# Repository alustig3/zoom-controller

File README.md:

# Table of Contents

- [What is this?](#what-is-this)
  - [Demo Video](#demo-video)
- [How do I use it?](#how-do-i-use-it)
  - [Turning on](#turning-on)
  - [Connecting to Bluetooth](#connecting-to-bluetooth)
  - [Turning off](#turning-off)
  - [Disconnecting Bluetooth](#disconnecting-bluetooth)
  - [Adjust volume](#adjust-volume)
  - [Controlling Zoom!](#controlling-zoom)
  - [Switching modes](#switching-modes)
- [Getting fancy](#getting-fancy)
  - [Desktop notifications](#desktop-notifications)
  - [YouTube controller](#youtube-controller)
- [How do I make one?](#how-do-i-make-one)
  - [Stand](#stand)
  - [Electronics](#electronics)
  - [Additional hardware](#additional-hardware)
  - [Software](#software)
- [Feedback](#feedback)
# What is this?
I, like many others, found myself using Zoom video conference software a lot this past year. 
I created this device to make interacting with Zoom faster and more pleasant. 

- The Zoom Controller connects with your computer over Bluetooth and emulates keyboard key presses
- Works with Mac and Windows
- Five buttons are setup to emulate the default keyboard shortcuts in Zoom
- A knob controls the computer's media volume
- Powered by two AA batteries
- The circuit board mounts to a bent piece of 12 Gauge steel
- Bonus features include desktop notifications and YouTube Mode (see [getting fancy](#getting-fancy))

## Demo video
<div style="">
  
</div>

# How do I use it? 
- [Turning on](#turning-on)
- [Connecting to Bluetooth](#connecting-to-bluetooth)
- [Turning off](#turning-off)
- [Disconnecting Bluetooth](#disconnecting-bluetooth)
- [Controlling Zoom!](#controlling-zoom)
- [Switching modes](#switching-modes)

## Turning on
Press and hold the **VOLUME** knob to turn on. 
You can let go of the knob as soon as you see it light up red. 
The knob will "breathe" red light while it is trying to connect to Bluetooth. Once connected, the knob will turn green. 

The controller will automatically turn off after 20 seconds attempting and failing to connect.

## Connecting to Bluetooth
If it is the first time using Zoom Controller, you will need to add it your computer's list of Bluetooth devices. Once added, the Zoom Controller will automatically connect when turned on and within range of your computer.
### Mac
- Open System Preferences -> Bluetooth
- [Turn on](#turning-on) Zoom Controller
- When it appears in your list of Bluetooth devices, click connect. Once connected, the light will turn green, and you're good to go!
- There may be a "Keyboard Setup Assistant" window that pops up asking you to press a key to identify your keyboard. You can ignore this and just close the window.

### Windows
- Search for "bluetooth" in the search bar and select "Bluetooth and other devices settings"
- At the top, click "Add Bluetooth or other device"
- Click "Bluetooth - Mice, keyboards, pens or other kinds of Bluetooth devices"
- Turn on the Zoom Controller by pressing the **VOLUME** knob until a red light appears
- Zoom controller should appear in the "Add a device" list

## Turning off
Press and hold the **LEAVE** button. The volume knob's light will turn off when the controller is powered off.

There is an idle clock always counting. 
Every time you press a button or rotate the knob, the idle clock is reset to 0. 
If the idle clock reaches 60 minutes, the controller will automatically turn itself off to save battery.

## Disconnecting Bluetooth
The Zoom Controller can only be connected to one device at a time. If you want to use it with a different computer it is important that you first remove it from its current computer's Bluetooth device list.
### Mac
- Open to System Prefrences -> Bluetooth
- Right click on the Zoom Controller and select "Remove"
### Windows
- Search for "bluetooth" in the search bar and select "Bluetooth and other devices settings"
- Under the "Mouse, keyboard, & pen" click "Zoom Controller" and then click "Remove device"

## Controlling Zoom!

### Adjust volume
Rotate the **VOLUME** knob clockwise to increase volume, counterclockwise to decrease volume.

### Send Shortcuts on Mac
The five buttons are setup to execute the following Zoom functions by emulating their default keyboard shortcuts.

| Button | Zoom Function             | Emulated Mac Keypress                           |
|--------|---------------------------|-------------------------------------------------|
| Mic    | mute/unmute microphone    | shift + command + a                             |
| Camera | start/stop video          | shift + command + v                             |
| Share  | start/stop screen sharing | shift + command + s                             |
| View   | speaker/gallery view      | shift + command + w                             |
| Leave* | leave meeting             | command + w, followed by Return to confirm leave |

### Send Shortcuts on Windows

| Button              | Zoom Function             | Emulated Windows Keypress                  |
|---------------------|---------------------------|--------------------------------------------|
| Mic                 | mute/unmute microphone    | alt + a                                    |
| Camera              | start/stop video          | alt + v                                    |
| Share               | start/stop screen sharing | alt + s                                    |
| View (single press) | speaker view              | alt + F1                                   |
| View (double press) | gallery view              | alt + F2                                   |
| Leave*              | leave meeting             | alt + q, folowed by Enter to confirm leave |

**Zoom Controller will automatically turn off 8 seconds after pressing **LEAVE**, unless you keep it awake by pressing a button or rotating the knob within those 8 seconds. 
The knob will blink green indicating that the controller is about to turn itself off.*

## Switching modes
Keyboard shortcuts sent by Zoom Controller depend on which operating system and which application is being used. 
Because of this, there are 4 different modes that Zoom controller can be in. 
There are 2 operating system modes (Mac, Windows) and 2 application modes (Zoom, YouTube*).

**see [YouTube Controller](#youtube-controller)*

### Mac mode
- Press down the **VOLUME** button. 
- While holding the **VOLUME** button, press and hold the **MIC** button for 2 seconds
- The **VOLUME** button will blink **3** times indicating it is now in Mac mode. You can release both buttons.

### Windows mode
- Press down the **VOLUME** button. 
- While holding the **VOLUME** button, press and hold the **CAMERA** button for 2 seconds
- The **VOLUME** button will blink **7** times indicating it is now in Windows mode. You can release both buttons.

### Switch into Zoom mode
- Press and hold the VOLUME knob
- Press and release the MIC button

### Switch into YouTube mode
- Press and hold the VOLUME knob
- Press and release the CAMERA button

# Getting fancy
## Desktop notifications
You can enable Zoom Controller notifications show up on your desktop. The following notifications will appear when relevant:
- "Mac Mode"
- "Windows Mode"
- "Zoom Mode"
- "YouTube Mode"
- "Controller has been idle for awhile and will soon turn itself off. Press any button or rotate knob to keep awake"
### Mac notifications setup
- Download [Hammerspoon](https://www.hammerspoon.org/).
- Click the Hammerspooon menu bar icon and select "Open Config".
- Add the following to your `init.lua` file:
```lua
hs.hotkey.bind({"cmd", "alt", "ctrl"}, "F1", function()
  hs.alert.show("Mac Mode")
end)

hs.hotkey.bind({"cmd", "alt", "ctrl"}, "F2", function()
  hs.alert.show("Windows Mode")
end)

hs.hotkey.bind({"cmd","alt","ctrl"}, "F3", function()
  hs.notify.new({title="Zoom Controller Idle", informativeText="Controller will turn off soon\nPress any key to keep awake"}):send()
end))

hs.hotkey.bind({"cmd", "alt", "ctrl"}, "F4", function()
  hs.alert.show("Zoom Mode")
end)

hs.hotkey.bind({"cmd", "alt", "ctrl"}, "F5", function()
  hs.alert.show("YouTube Mode")
end)

```
- Save your changes to the `inti.lua` file then click the Hammerspoon menu bar icon and select "Reload Config" 
### Windows notifications setup
- Download [AutoHotkey](https://www.autohotkey.com/)
- Download this [zoom_controller_notifications.ahk](docs/zoom_controller_notifications.ahk) script file
- Once the script file is downloaded, double click it to begin running the script
- If you want the script to automatically run every time you turn on your computer, follow instructions [here](https://www.autohotkey.com/docs/FAQ.htm#Startup)

## YouTube controller
I've found this device to be super useful for watching online videos.

### Installation
- Add an extension called **Video Speed Controller** to your web browser
  - [Chrome extension](https://chrome.google.com/webstore/detail/video-speed-controller/nffaoalbilbmmfgbnbgppjihopabppdk)
  - [Firefrox extension](https://addons.mozilla.org/en-US/firefox/addon/videospeed/?utm_source=addons.mozilla.org&utm_medium=referral&utm_content=search)

### Controlling YouTube
#### Send Shortcuts
| Button | YouTube Function  | Emulated Keypress |
|--------|-------------------|-------------------|
| Mic    |                   |                   |
| Camera | rewind 10s        | z                 |
| Share  | fast forward 10s  | x                 |
| View   | toggle fullscreen | f                 |
| Leave  | play/pause        | spacebar          |

#### Adjust playback speed
- Increase/decrease the video playback speed by rotating the VOLUME knob clockwise/counterclockwise
- Toggle between 1X speed and your adjusted playback speed by clicking the VOLUME knob
#### Adjust Volume
- Increase/decrease the volume by pressing and holding down MIC then rotating the VOLUME knob clockwise/counterclockwise.

# How do I make one?
## Stand
- File for lasercutting: [stand.dxf](https://alustig3.github.io/zoom-controller/stand.dxf)
- 0.1" thick (12Ga) steel cut and bent at https://www.oshcut.com/

## Electronics
### Bill of Materials
| Qty | Reference          | Description       | Value/MPN                                                                                                    | 
|-----|--------------------|-------------------|--------------------------------------------------------------------------------------------------------------|
| 1   | BT1                | Battery Holder    | [2462](https://www.digikey.com/product-detail/en/keystone-electronics/2466/36-2466-ND/303815)                | 
| 1   | C1                 | 0805 Capacitor    | 10nF                                                                                                         | 
| 1   | D1                 | Schottky Diode    | [BAT54C](http://www.diodes.com/_files/datasheets/ds11005.pdf)                                                | 
| 2   | H3, H4             | Threaded Standoff | [4207](https://www.adafruit.com/product/4207)                                                                | 
| 1   | Q1                 | P-Channel MOSFET  | [FDN340P](https://www.digikey.com/products/en?keywords=FDN340PCT-ND)                                         | 
| 1   | Q2                 | N-Channel MOSFET  | [BSS123](https://www.digikey.com/products/en?keywords=BSS123LT1GOSCT-ND)                                     | 
| 1   | R1                 | 0805 Resistor     | 100KΩ                                                                                                        | 
| 1   | R2                 | 0805 Resistor     | 10KΩ                                                                                                         | 
| 1   | R3                 | 0805 Resistor     | 330Ω                                                                                                         | 
| 1   | R4                 | 0805 Resistor     | 1MΩ                                                                                                          | 
| 5   | S1, S2, S3, S4, S5 | Tactile Button    | [DD-15326](https://www.sparkfun.com/products/15326)                                                          | 
| 1   | SW1                | Rotary Encoder    | [COM-15140](https://www.sparkfun.com/products/15140)                                                         | 
| 1   | U1                 | Microcontroller   | [ESP32-WROOM-32E](https://www.digikey.com/en/products/detail/espressif-systems/ESP32-WROOM-32E-4MB/11613125) | 

<div style="">
  
</div>

## Additional hardware
- 6mm long M3 x 0.5mm screws: https://www.mcmaster.com/92095A179/
- Clear plastic knob for rotary encoder: https://www.sparkfun.com/products/10597

## Software
The code was developed using [PlatformIO](https://docs.platformio.org/en/latest/boards/espressif32/esp32dev.html).
An [ESP-PROG](https://www.digikey.com/en/products/detail/espressif-systems/ESP-PROG/10259352?s=N4IgTCBcDaIKYGcAOBaJAnA9gcxAXQF8g) was used to program the ESP32 microcontroller.
You should be able to use the platform.ini file from this repository, you'll just need to change the upload port. 
The platform.ini will automatically download the requisite [ESP32-BLE-Keyboard](https://github.com/T-vK/ESP32-BLE-Keyboard) library and ESP32 and Arduino frameworks.
# Feedback
If people are interested, I may consider buying some parts in bulk and selling the controllers on [Tindie](https://www.tindie.com/) or [Etsy](https://www.etsy.com/) ¯\\\_(ツ)_/¯

If you have questions, comments, or are interested in buying a Zoom Controller:

<div style="height:100px;">
  
</div>

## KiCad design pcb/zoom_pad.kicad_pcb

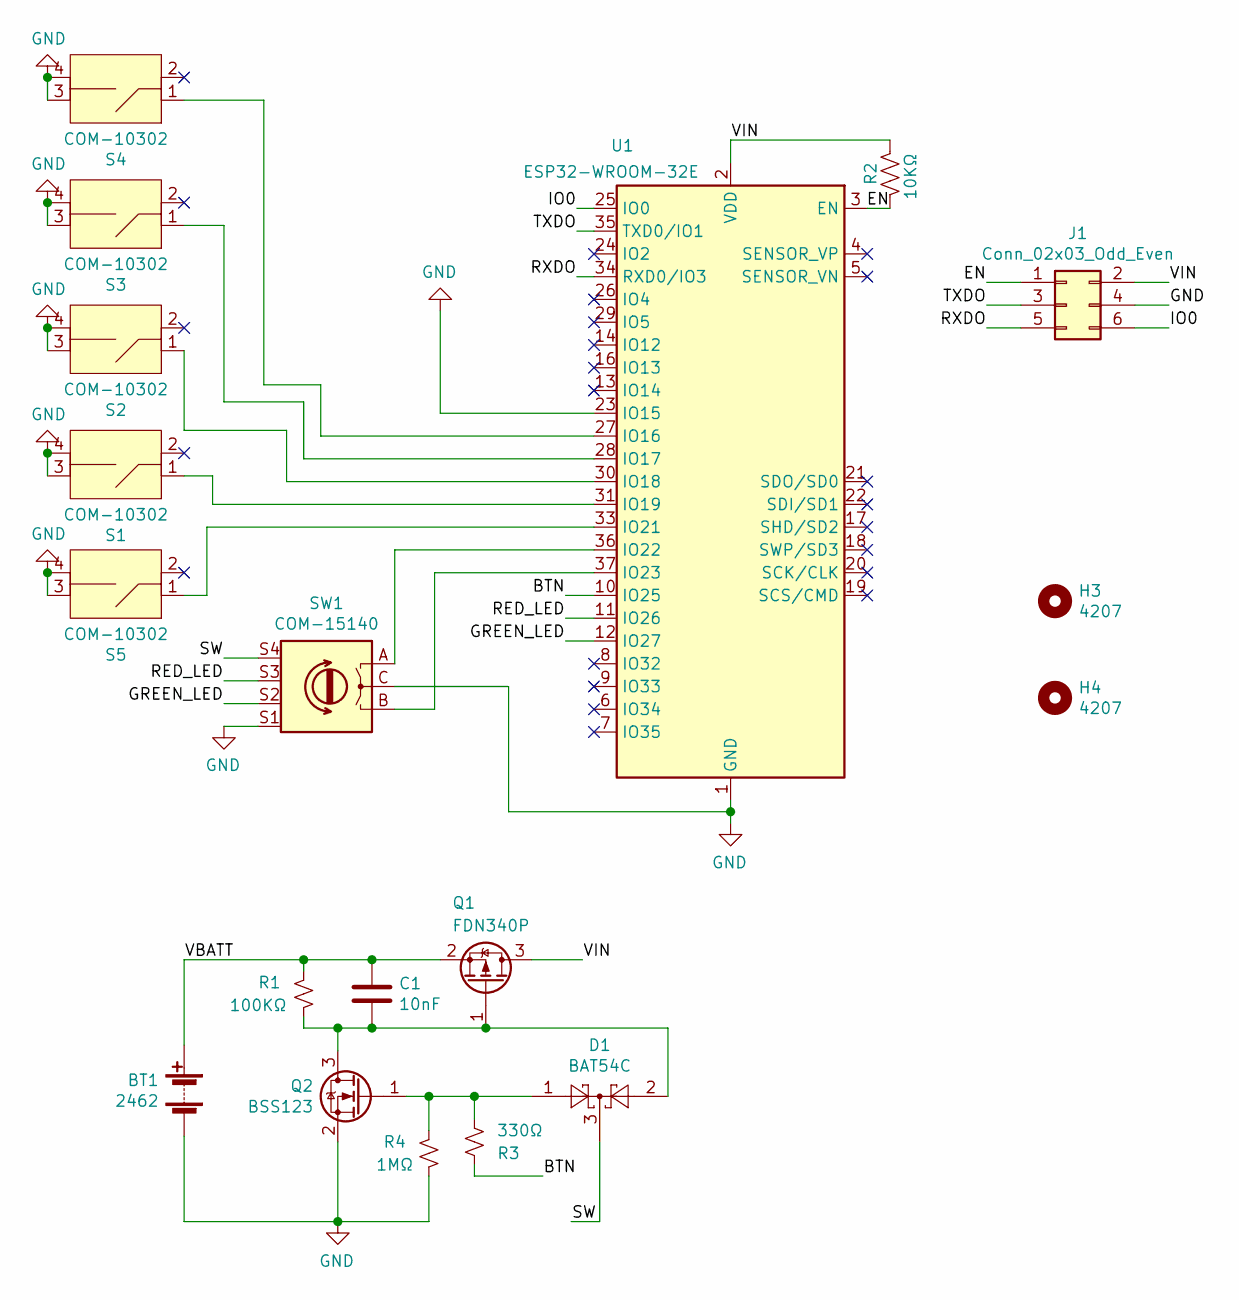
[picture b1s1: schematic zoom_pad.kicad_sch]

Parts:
BT1: 2462; BatteryHolder_Keystone_2462_2xAA
C1: 10nF; C_0805_2012Metric
D1: BAT54C; SOT-23; LCSC C397610
H3, H4: 4207; standoff_nut
J1: Conn_02x03_Odd_Even; Tag-Connect_TC2030-IDC-NL_2x03_P1.27mm_Vertical
Q1: FDN340P; SOT-23; LCSC C75469
Q2: BSS123; SOT-23; LCSC C431506
R1: 100KΩ; R_0805_2012Metric
R2: 10KΩ; R_0805_2012Metric
R3: 330Ω; R_0805_2012Metric
R4: 1MΩ; R_0805_2012Metric
S1, S2, S3, S4, S5: COM-10302; sparkfun_tactile_color
SW1: COM-15140; RG_Encoder
U1: ESP32-WROOM-32E; ESP32-WROOM-32; LCSC C701341

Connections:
/BTN: R3.1, U1.10 (IO25)
/EN: J1.1, R2.1, U1.3 (EN)
/GREEN_LED: SW1.S2, U1.12 (IO27)
/IO0: J1.6, U1.25 (IO0)
/RED_LED: SW1.S3, U1.11 (IO26)
/RXDO: J1.5, U1.34 (RXD0/IO3)
/SW: D1.3, SW1.S4
/TXDO: J1.3, U1.35 (TXD0/IO1)
/VBATT: BT1.1 (+), C1.1, Q1.2 (S), R1.2
/VIN: J1.2, Q1.3 (D), R2.2, U1.2 (VDD)
GND: BT1.2 (-), J1.4, Q2.2 (S), R4.1, S1.3 (out1), S1.4 (out2), S2.3 (out1), S2.4 (out2), S3.3 (out1), S3.4 (out2), S4.3 (out1), S4.4 (out2), S5.3 (out1), S5.4 (out2), SW1.C, SW1.S1, U1.1 (GND), U1.15 (GND), U1.23 (IO15), U1.38 (GND), U1.39 (GND)
unnamed: C1.2, D1.2, Q1.1 (G), Q2.3 (D), R1.1
unnamed: D1.1, Q2.1 (G), R3.2, R4.2
unnamed: S1.1 (in1), U1.31 (IO19)
unnamed: S2.1 (in1), U1.30 (IO18)
unnamed: S3.1 (in1), U1.28 (IO17)
unnamed: S4.1 (in1), U1.27 (IO16)
unnamed: S5.1 (in1), U1.33 (IO21)
unnamed: SW1.A, U1.36 (IO22)
unnamed: SW1.B, U1.37 (IO23)

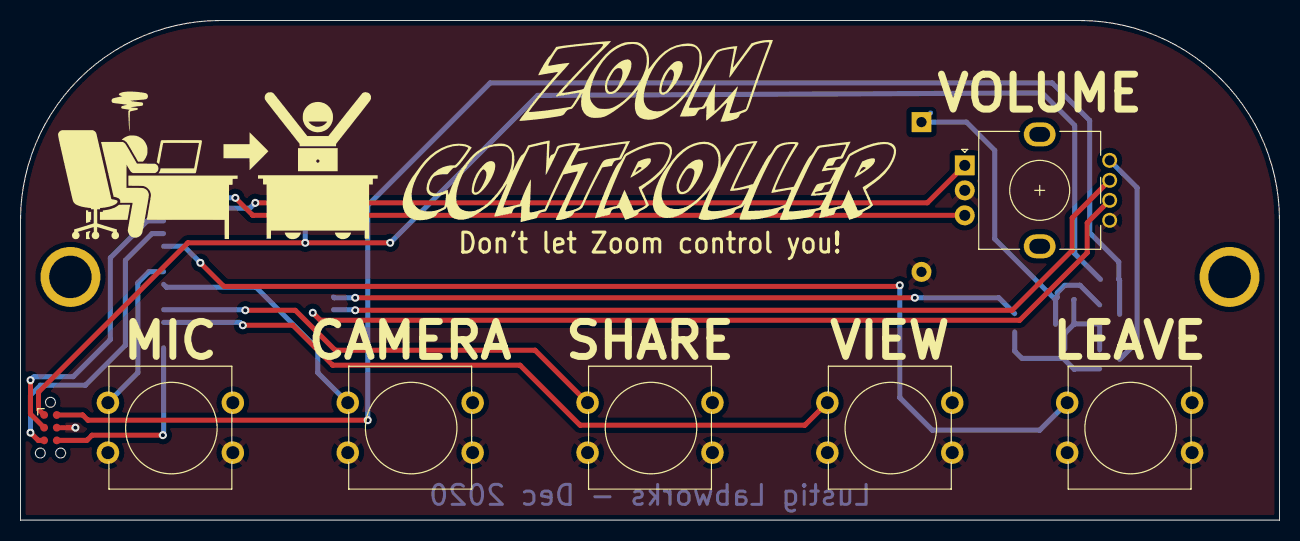
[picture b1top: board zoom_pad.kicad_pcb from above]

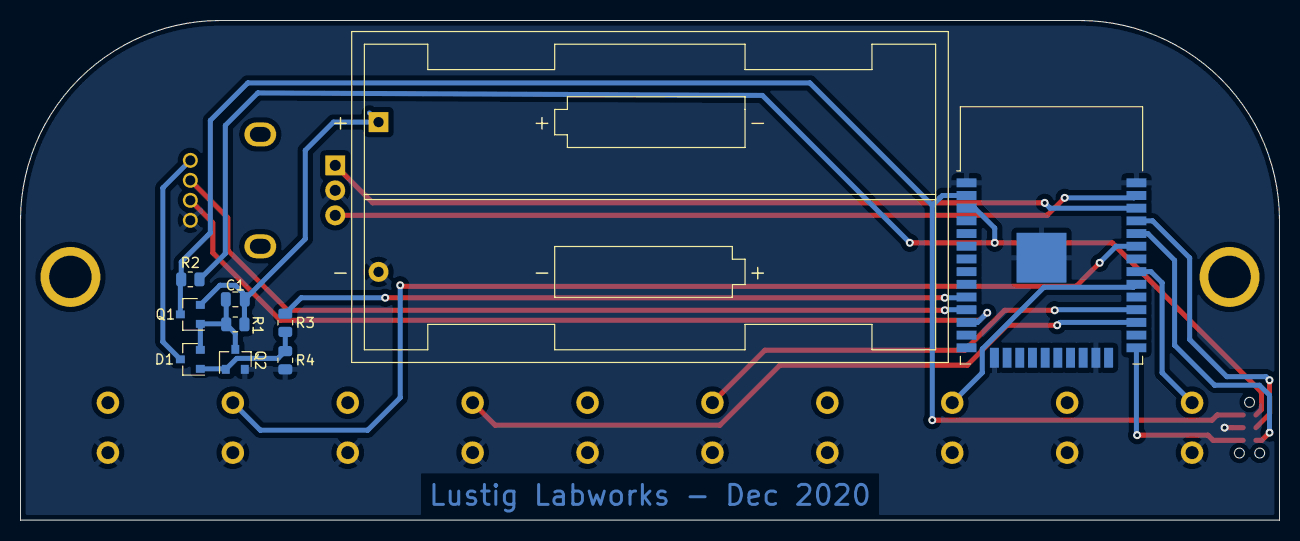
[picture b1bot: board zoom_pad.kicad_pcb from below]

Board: 2 copper layers, 126.0 x 50.0 mm, 19 parts (10 on the bottom side), 20 nets.

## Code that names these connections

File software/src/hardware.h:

// pin defines
const byte latch_BTN = 25;
const byte encoderPin1 = 22;
const byte encoderPin2 = 23;
const byte btn_1 = 19;
const byte btn_2 = 18;
const byte btn_3 = 17;
const byte btn_4 = 16;
const byte btn_5 = 21;
const byte red_LED = 26;
const byte green_LED = 27;

//knob
volatile int lastEncoded = 0;
int tempNow = 0,tempOld = 0;
const byte knob_sensitivity = 2;
const byte resolution = 8;
const byte redPWM = 0;
const byte greenPWM = 1;
const int freq = 500; // 5000 Khz produced a hum at 50% duty cycle, so brought this down
const byte knob_brightness = 100;


//hardware
void updateEncoder();
bool check_for_activity();
bool double_click( int btn_pin);
bool check_for_hold(int btn_pin, int hold_duration, void (*passed_fxn)());
bool check_for_hold(int btn_pin, int hold_duration, void (*passed_fxn)(os),os newos);
void blink_yellow(int num_blinks);
void pulse();


void updateEncoder(){
  int MSB = digitalRead(encoderPin1); //MSB = most significant bit
  int LSB = digitalRead(encoderPin2); //LSB = least significant bit
  int encoded = (MSB << 1) |LSB; //converting the 2 pin value to single number
  int sum  = (lastEncoded << 2) | encoded; //adding it to the previous encoded value
  if(sum == 0b1101 || sum == 0b0100 || sum == 0b0010 || sum == 0b1011) tempNow++;
  if(sum == 0b1110 || sum == 0b0111 || sum == 0b0001 || sum == 0b1000) tempNow--;
  lastEncoded = encoded; //store this value for next time
}

bool check_for_activity(){
  if (tempNow-tempOld>knob_sensitivity){
    return true;
  }
  if (tempNow-tempOld<-knob_sensitivity){
    return true;
  }
  if (!digitalRead(latch_BTN)){//
    return true;
  }
  if (!digitalRead(btn_1)){//
    return true;
  }
  if (!digitalRead(btn_2)){//
    return true;
  }
  if (!digitalRead(btn_3)){//
    return true;
  }
  if (!digitalRead(btn_4)){//
    return true;
  }
  return false;
}

bool double_click(int btn_pin){
  while(!digitalRead(btn_pin)){
    delay(2); //in first press
  }
  int second_press_timer = 0;
  bool double_clicked = false;
  while(second_press_timer < 120){
    delay(1);
    second_press_timer++;
    if (!digitalRead(btn_pin)){
      Serial.println("Double click!");
      double_clicked = true;
      break;
    }
  }
  Serial.println(second_press_timer);
  return double_clicked;
}

bool check_for_hold(int btn_pin, int hold_duration, void (*passed_fxn)()){
    int hold_count = 0;
    bool hold_threshold_met = false;
    while(!digitalRead(btn_pin)){
      delay(1);
      hold_count++;
      if (hold_count>hold_duration){
        passed_fxn();
        while(!digitalRead(btn_pin)){
          delay(1);
        }
        hold_threshold_met = true;
      }
    }
    return hold_threshold_met;
}

bool check_for_hold(int btn_pin, int hold_duration, void (*passed_fxn)(os),os newos){
    int hold_count = 0;
    bool hold_threshold_met = false;
    while(!digitalRead(btn_pin)){
      delay(1);
      hold_count++;
      if (hold_count>hold_duration){
        passed_fxn(newos);
        while(!digitalRead(btn_pin)){
          delay(1);
        }
        hold_threshold_met = true;
      }
    }
    return hold_threshold_met;
}

void blink_yellow(int num_blinks){
  for (int i=0; i<num_blinks;i++){
    ledcWrite(greenPWM,0);
    delay(250);
    ledcWrite(greenPWM,knob_brightness);
    delay(250);
  }
}

void pulse(){
  for (int i = 255; i >knob_brightness; i--){
    ledcWrite(greenPWM,i);
    delay(1);
  }
}

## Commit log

2020-12-07 initial software setup
2020-12-07 working encoder inputs
2020-12-07 rotation and button click
2020-12-07 Bluetooth keyboard working
2020-12-07 encoder LEDs working with PWM
2020-12-09 PCB v1
2020-12-17 working code on bodged v1 PCB
2020-12-19 PCB v1.1
2020-12-20 New firmware features
    - breathes red when connecting at startup
    - button presses pulse green LED
    - double click knob to turn off
2020-12-27 firmware update
    - added code for 5th button (PCB v1.1)
    - zoom mode or youtube mode depending on if 1st button is held down during startup
2020-12-29 Firmware update
    - double click time limit is now smaller
    - can now switch between modes by double clicking button 2
    - when mode is switched, hammerspoon keys are sent so a message pops up on computer screen
    - in youtube mode, hold button 1 and rotate knob to adjust volume
2020-12-29 Extend battery life
    - shutdown after trying unsuccessfully to connect to bluetooth for 20 seconds
    - removed brown out detection (maybe bad idea...)
    - idle time is now 5 minutes. Warning notification is sent to mac 10seconds before shutdown
2020-12-29 interface changes
    - hold down button 5 to turn off
    - double click button 1 to switch modes
    - press and turn knob to adjust volume during youtube mode
2021-01-01 test
2021-01-08 make files public
2021-01-08 rough draft of documentation
2021-01-08 Readme update
2021-01-08 readme updates
2021-01-08 Added missing gif
2021-01-13 added demo video
2021-01-13 fix demo video not playing?
2021-01-13 video fixed
2021-01-14 Doc update
    - added gif for connecting to bluetooth on windows
    - added download link for stand.dxf
2021-01-28 shutdown warning updates
    - shortened blinking warning period to 5s
    - can skip warning period and immediately shutdown by pressing "leave" button
2021-04-24 fully exit zoom when pressing leave
2021-04-24 Doc update
2021-07-11 removed excessive internal links
2021-07-14 corrected error in youtube shortcut table
